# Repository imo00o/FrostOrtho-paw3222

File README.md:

# FrostOrtho-paw3222

## Credits
このプロジェクトは、badjeff氏による [paw3222-pcb](https://github.com/badjeff/paw3222-pcb) の設計を元に作成・改変したものです。

## License
このプロジェクト（改変部分を含む）は、ベースプロジェクトと同様に **[CERN-OHL-P v2](https://github.com/badjeff/paw3222-pcb/blob/main/LICENSE)** ライセンスの下で公開されています。

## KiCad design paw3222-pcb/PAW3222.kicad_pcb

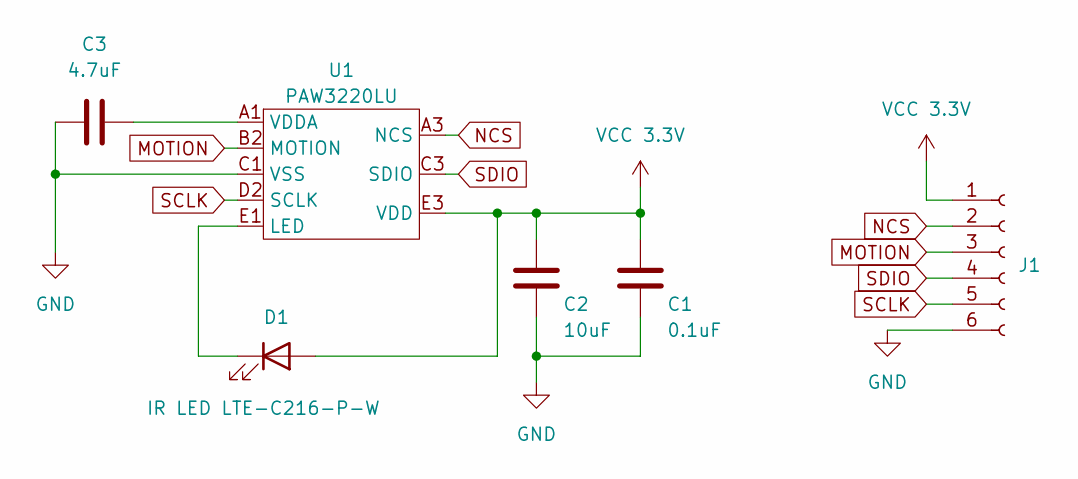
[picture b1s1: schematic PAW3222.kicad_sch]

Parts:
C1: 0.1uF; C_0402_1005Metric
C2: 10uF; C_0402_1005Metric
C3: 4.7uF; C_0402_1005Metric
D1: IR LED LTE-C216-P-W; LTE-C216-P-W; LCSC C2942980
J1: Conn_01x06_Socket; ffc_connector_1_6_0.5mm
U1: PAW3220LU; PAW3222LU; LCSC C9900022540

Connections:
GND: C1.2, C2.2, C3.2, J1.6, U1.C1 (VSS)
MOTION: J1.3, U1.B2 (MOTION)
NCS: J1.2, U1.A3 (NCS)
unnamed: D1.1 (K), U1.E1 (LED)
unnamed: C3.1, U1.A1 (VDDA)
SCLK: J1.5, U1.D2 (SCLK)
SDIO: J1.4, U1.C3 (SDIO)
VCC 3.3V: C1.1, C2.1, D1.2 (A), J1.1, U1.E3 (VDD)

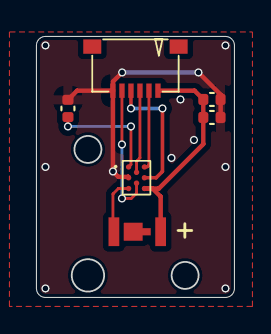
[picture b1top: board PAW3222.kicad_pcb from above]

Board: 2 copper layers, 10.9 x 14.5 mm, 6 parts (0 on the bottom side), 8 nets.

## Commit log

2026-04-25 first comomit
2026-04-25 add led
2026-04-29 基板修正
2026-05-12 pcb最新化
